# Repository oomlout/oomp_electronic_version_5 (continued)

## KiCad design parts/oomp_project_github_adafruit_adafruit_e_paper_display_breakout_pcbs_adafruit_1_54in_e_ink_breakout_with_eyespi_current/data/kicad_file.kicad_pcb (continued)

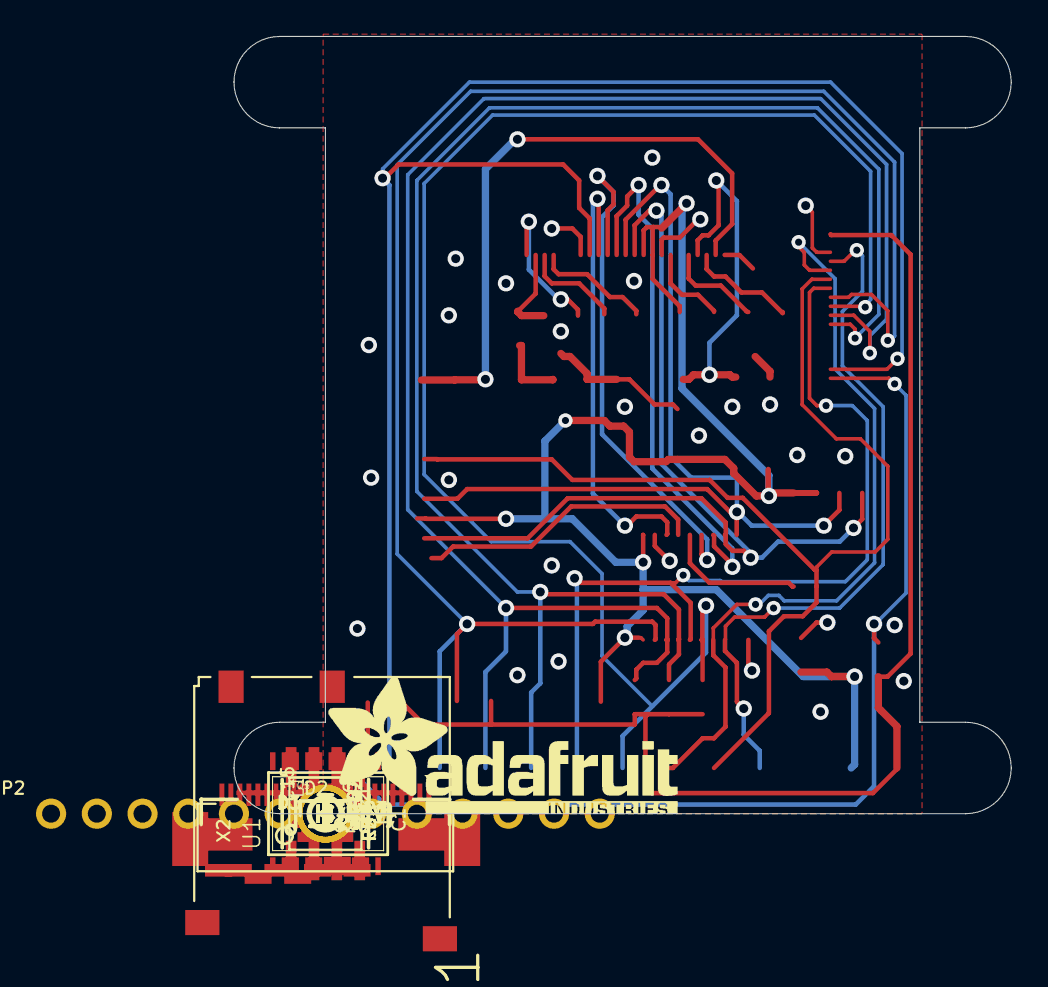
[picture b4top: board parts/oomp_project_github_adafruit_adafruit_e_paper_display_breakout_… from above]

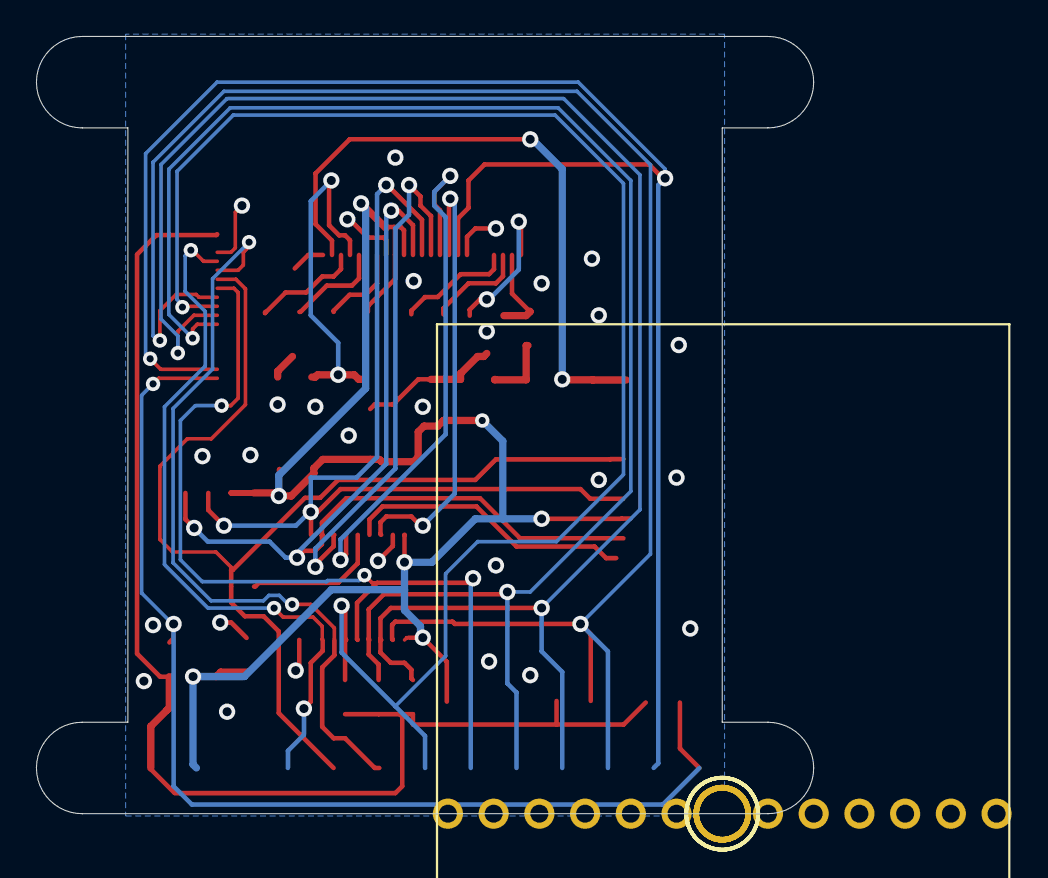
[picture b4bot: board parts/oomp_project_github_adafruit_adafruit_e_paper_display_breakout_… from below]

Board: 2 copper layers, 43.2 x 43.2 mm, 70 parts (18 on the bottom side), 32 nets.

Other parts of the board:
PLABEL0: PLABEL0
PLABEL1: PLABEL1
PLABEL2: PLABEL2
PLABEL3: PLABEL3
PLABEL4: PLABEL4
PLABEL5: PLABEL5
PLABEL6: PLABEL6
PLABEL7: PLABEL7
PLABEL8: PLABEL8
PLABEL9: PLABEL9
PLABEL10: PLABEL10
PLABEL11: PLABEL11
PLABEL12: PLABEL12
PLABEL13: PLABEL13
PLABEL14: PLABEL14
PLABEL15: PLABEL15
PLABEL16: PLABEL16
PLABEL17: PLABEL17
PLABEL18: PLABEL18
PLABEL19: PLABEL19
PLABEL20: PLABEL20
PLABEL21: PLABEL21
PLABEL22: PLABEL22
PLABEL23: PLABEL23
PLABEL24: PLABEL24
PLABEL25: PLABEL25
PLABEL26: PLABEL26
PLABEL27: PLABEL27
U$9: PCBFEAT-REV-040
U$28: ADAFRUIT_TEXT_20MM

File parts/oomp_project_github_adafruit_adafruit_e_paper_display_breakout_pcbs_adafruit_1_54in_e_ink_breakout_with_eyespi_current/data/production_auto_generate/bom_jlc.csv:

Comment,Designator,Footprint,LCSC Part #
,JP2,Adafruit 1.54in eInk Breakout with EYESPI-import-fps:1X13_ROUND_70,C2894936
,U$28,Adafruit 1.54in eInk Breakout with EYESPI-import-fps:ADAFRUIT_TEXT_20MM,
,U$9,Adafruit 1.54in eInk Breakout with EYESPI-import-fps:PCBFEAT-REV-040,
,PLABEL0,Adafruit 1.54in eInk Breakout with EYESPI-import-fps:PLABEL0,
,PLABEL1,Adafruit 1.54in eInk Breakout with EYESPI-import-fps:PLABEL1,
,PLABEL10,Adafruit 1.54in eInk Breakout with EYESPI-import-fps:PLABEL10,
,PLABEL11,Adafruit 1.54in eInk Breakout with EYESPI-import-fps:PLABEL11,
,PLABEL12,Adafruit 1.54in eInk Breakout with EYESPI-import-fps:PLABEL12,
,PLABEL13,Adafruit 1.54in eInk Breakout with EYESPI-import-fps:PLABEL13,
,PLABEL14,Adafruit 1.54in eInk Breakout with EYESPI-import-fps:PLABEL14,
,PLABEL15,Adafruit 1.54in eInk Breakout with EYESPI-import-fps:PLABEL15,
,PLABEL16,Adafruit 1.54in eInk Breakout with EYESPI-import-fps:PLABEL16,
,PLABEL17,Adafruit 1.54in eInk Breakout with EYESPI-import-fps:PLABEL17,
,PLABEL18,Adafruit 1.54in eInk Breakout with EYESPI-import-fps:PLABEL18,
,PLABEL19,Adafruit 1.54in eInk Breakout with EYESPI-import-fps:PLABEL19,
,PLABEL2,Adafruit 1.54in eInk Breakout with EYESPI-import-fps:PLABEL2,
,PLABEL20,Adafruit 1.54in eInk Breakout with EYESPI-import-fps:PLABEL20,
,PLABEL21,Adafruit 1.54in eInk Breakout with EYESPI-import-fps:PLABEL21,
,PLABEL22,Adafruit 1.54in eInk Breakout with EYESPI-import-fps:PLABEL22,
,PLABEL23,Adafruit 1.54in eInk Breakout with EYESPI-import-fps:PLABEL23,
,PLABEL24,Adafruit 1.54in eInk Breakout with EYESPI-import-fps:PLABEL24,
,PLABEL25,Adafruit 1.54in eInk Breakout with EYESPI-import-fps:PLABEL25,
,PLABEL26,Adafruit 1.54in eInk Breakout with EYESPI-import-fps:PLABEL26,
,PLABEL27,Adafruit 1.54in eInk Breakout with EYESPI-import-fps:PLABEL27,
,PLABEL3,Adafruit 1.54in eInk Breakout with EYESPI-import-fps:PLABEL3,
,PLABEL4,Adafruit 1.54in eInk Breakout with EYESPI-import-fps:PLABEL4,
,PLABEL5,Adafruit 1.54in eInk Breakout with EYESPI-import-fps:PLABEL5,
,PLABEL6,Adafruit 1.54in eInk Breakout with EYESPI-import-fps:PLABEL6,
,PLABEL7,Adafruit 1.54in eInk Breakout with EYESPI-import-fps:PLABEL7,
,PLABEL8,Adafruit 1.54in eInk Breakout with EYESPI-import-fps:PLABEL8,
,PLABEL9,Adafruit 1.54in eInk Breakout with EYESPI-import-fps:PLABEL9,
0.47ohm,R4,Adafruit 1.54in eInk Breakout with EYESPI-import-fps:0805_10MGAP,
100K,"R1,R2,R3,R5,R6",Adafruit 1.54in eInk Breakout with EYESPI-import-fps:0805-NO,C149504
10uF,"C15,C20,C21",Adafruit 1.54in eInk Breakout with EYESPI-import-fps:0805-NO,
10uH,L1,Adafruit 1.54in eInk Breakout with EYESPI-import-fps:INDUCTOR_4X4MM_NR401,
1uF,"C1,C2,C3,C4,C6,C7,C8,C16,C22,C23,C24",Adafruit 1.54in eInk Breakout with EYESPI-import-fps:0805-NO,
23K640-I/SN,U4,Adafruit 1.54in eInk Breakout with EYESPI-import-fps:SOIC8_150MIL,
4.7uF/25V,C5,Adafruit 1.54in eInk Breakout with EYESPI-import-fps:0805-NO,
74LVC245,U1,Adafruit 1.54in eInk Breakout with EYESPI-import-fps:TSSOP20,
AP2127K-3.3,U2,Adafruit 1.54in eInk Breakout with EYESPI-import-fps:SOT23-5,
EINK_24PIN_154IN,EINK1,Adafruit 1.54in eInk Breakout with EYESPI-import-fps:EINK_154IN,
EYE_SPI_DISPLAY_FLIP,X1,Adafruit 1.54in eInk Breakout with EYESPI-import-fps:EYE_SPI_DISPLAY_BOTCONTACT,
IRLML0100,Q5,Adafruit 1.54in eInk Breakout with EYESPI-import-fps:SOT23-3,
MBR0540,"D1,D2,D3",Adafruit 1.54in eInk Breakout with EYESPI-import-fps:SOD-123,
MICROSD,X2,Adafruit 1.54in eInk Breakout with EYESPI-import-fps:MICROSD,
